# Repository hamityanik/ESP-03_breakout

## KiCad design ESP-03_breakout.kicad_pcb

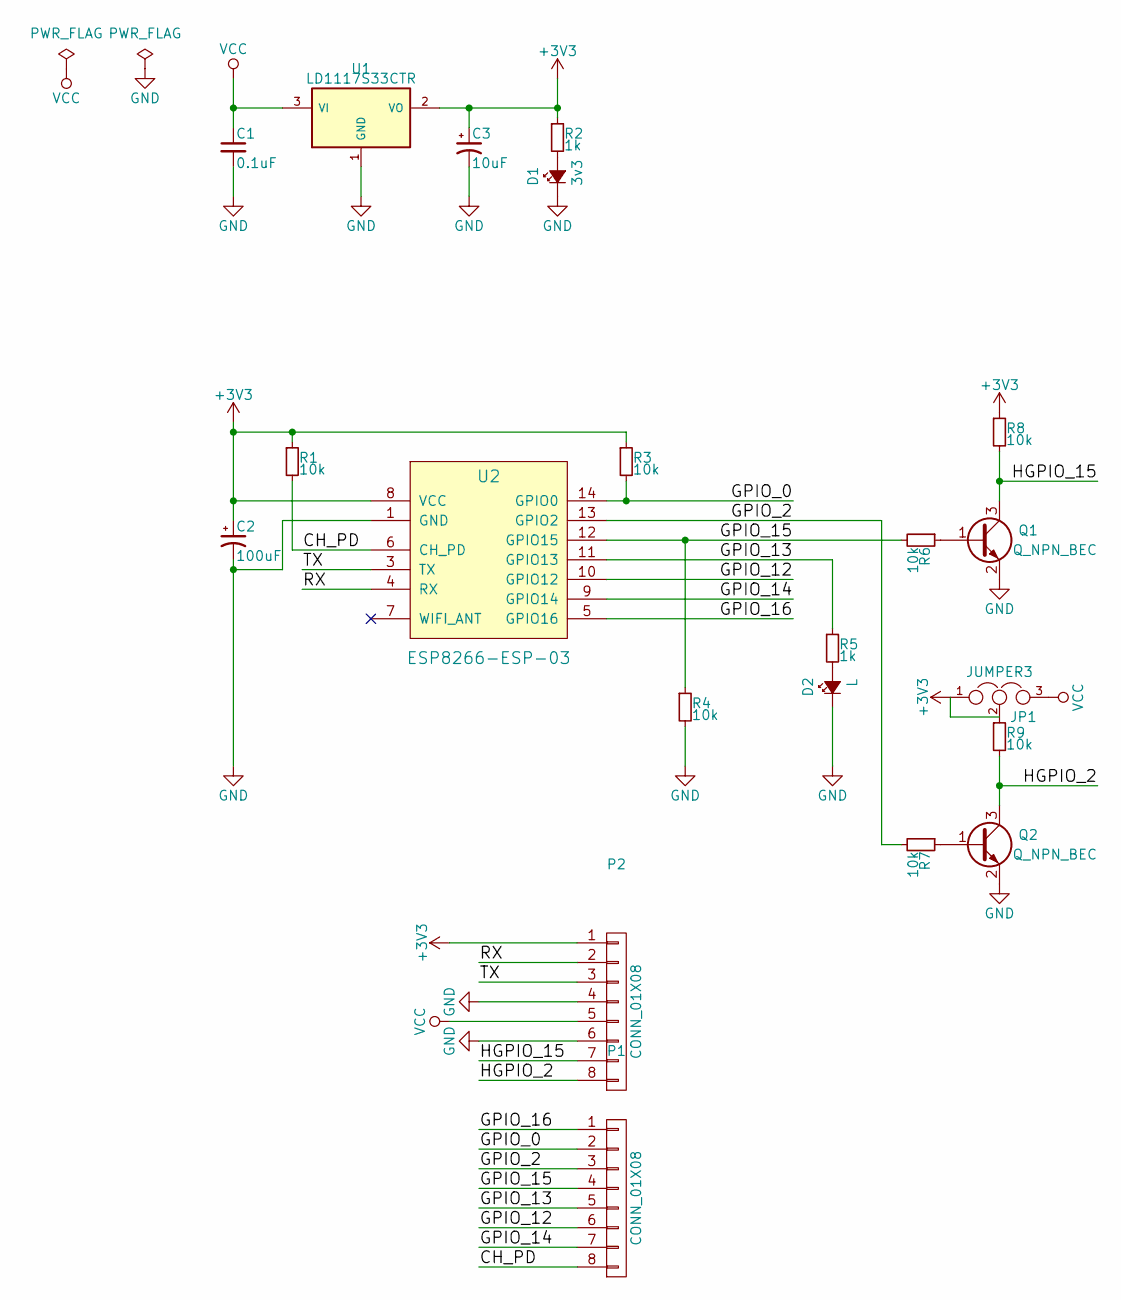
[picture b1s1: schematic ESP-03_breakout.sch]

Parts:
C1: 0.1uF; C_0805
C2: 100uF; CP_Tantalum_Case-B_EIA-3528-21_Reflow
C3: 10uF; CP_Tantalum_Case-S_EIA-3216-12_Reflow
D1: 3v3; LED_0805
D2: L; LED_0805
JP1: JUMPER3; SMD-solder-bridge-3pin
P1, P2: CONN_01X08; Pin_Header_Straight_1x08
Q1, Q2: Q_NPN_BEC; SOT-23
R1, R3, R4, R6, R7, R8, R9: 10k; R_0805
R2, R5: 1k; R_0805
U1: LD1117S33CTR; TO-252-2
U2: ESP8266-ESP-03

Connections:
+3V3: C2.1, C3.1, JP1.1, JP1.2, P2.1, R1.1, R2.1, R3.1, R8.1, R9.1, U1.2 (VO), U2.8 (VCC)
/CH_PD: P1.8, R1.2, U2.6 (CH_PD)
/GPIO_0: P1.2, R3.2, U2.14 (GPIO0)
/GPIO_2: P1.3, R7.2, U2.13 (GPIO2)
/GPIO_12: P1.6, U2.10 (GPIO12)
/GPIO_13: P1.5, R5.1, U2.11 (GPIO13)
/GPIO_14: P1.7, U2.9 (GPIO14)
/GPIO_15: P1.4, R4.1, R6.2, U2.12 (GPIO15)
/GPIO_16: P1.1, U2.5 (GPIO16)
/HGPIO_2: P2.8, Q2.3 (C), R9.2
/HGPIO_15: P2.7, Q1.3 (C), R8.2
/RX: P2.2, U2.4 (RX)
/TX: P2.3, U2.3 (TX)
GND: C1.2, C2.2, C3.2, D1.1 (K), D2.1 (K), P2.4, P2.6, Q1.2 (E), Q2.2 (E), R4.2, U1.1 (GND), U2.1 (GND)
unnamed: D1.2 (A), R2.2
unnamed: D2.2 (A), R5.2
unnamed: Q1.1 (B), R6.1
unnamed: Q2.1 (B), R7.1
VCC: C1.1, JP1.3, P2.5, U1.3 (VI)

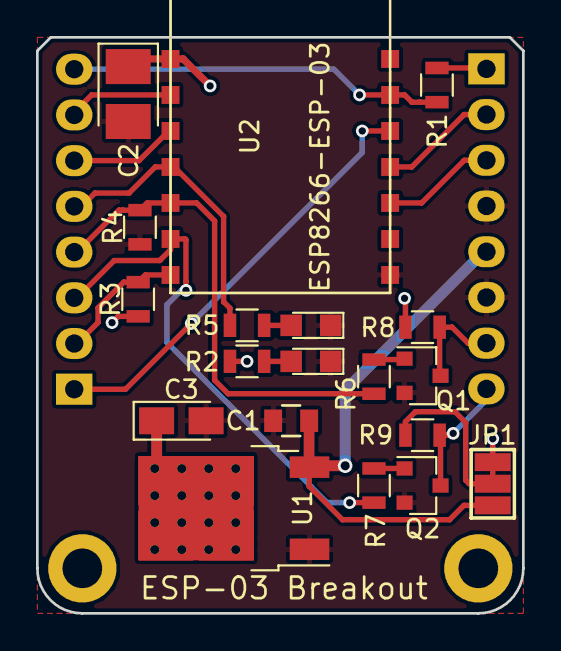
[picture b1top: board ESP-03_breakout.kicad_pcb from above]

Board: 2 copper layers, 27.0 x 32.0 mm, 21 parts (0 on the bottom side), 19 nets.

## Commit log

2018-01-31 Schematic PDF added
2018-01-31 Photo added
